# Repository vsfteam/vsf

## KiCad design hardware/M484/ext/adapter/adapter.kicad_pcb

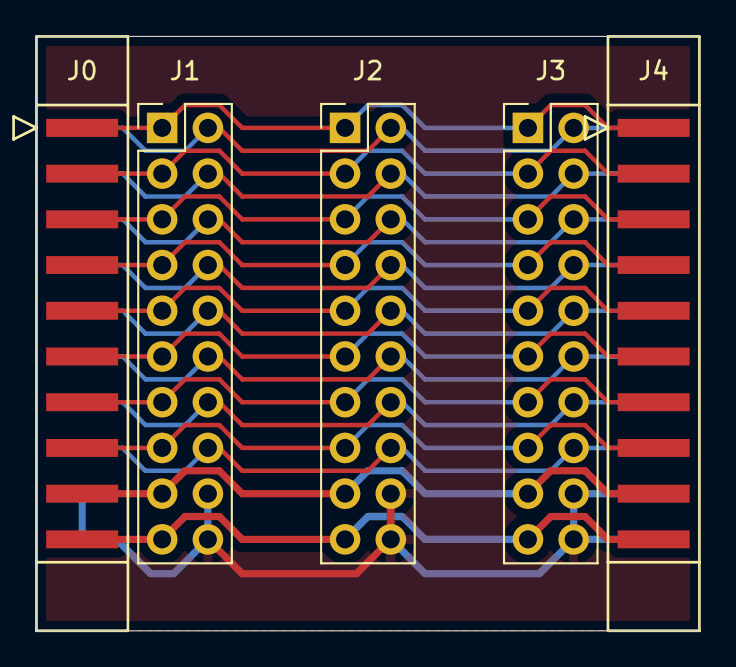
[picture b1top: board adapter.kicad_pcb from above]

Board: 2 copper layers, 36.8 x 33.0 mm, 5 parts (0 on the bottom side), 19 nets.

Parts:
J0, J4: Conn_02x10_Odd_Even; PinSocket_2x10_P2.54mm_Horizontal_2Layer
J1, J2, J3: Conn_02x10_Odd_Even; PinHeader_2x10_P2.54mm_Vertical

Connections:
/GND: J0.18, J0.20, J1.18, J1.20, J2.18, J2.20, J3.18, J3.20, J4.18, J4.20
/PB.0: J0.1, J1.1, J2.1, J3.1, J4.1
/PB.1: J0.2, J1.2, J2.2, J3.2, J4.2
/PB.2: J0.3, J1.3, J2.3, J3.3, J4.3
/PB.3: J0.4, J1.4, J2.4, J3.4, J4.4
/PB.4: J0.5, J1.5, J2.5, J3.5, J4.5
/PB.5: J0.6, J1.6, J2.6, J3.6, J4.6
/PB.6: J0.7, J1.7, J2.7, J3.7, J4.7
/PB.7: J0.8, J1.8, J2.8, J3.8, J4.8
/PB.8: J0.9, J1.9, J2.9, J3.9, J4.9
/PB.9: J0.10, J1.10, J2.10, J3.10, J4.10
/PB.10: J0.11, J1.11, J2.11, J3.11, J4.11
/PB.11: J0.12, J1.12, J2.12, J3.12, J4.12
/PB.12: J0.13, J1.13, J2.13, J3.13, J4.13
/PB.13: J0.14, J1.14, J2.14, J3.14, J4.14
/PB.14: J0.15, J1.15, J2.15, J3.15, J4.15
/PB.15: J0.16, J1.16, J2.16, J3.16, J4.16
/VCC: J0.17, J1.17, J2.17, J3.17, J4.17
/VCC5V: J0.19, J1.19, J2.19, J3.19, J4.19

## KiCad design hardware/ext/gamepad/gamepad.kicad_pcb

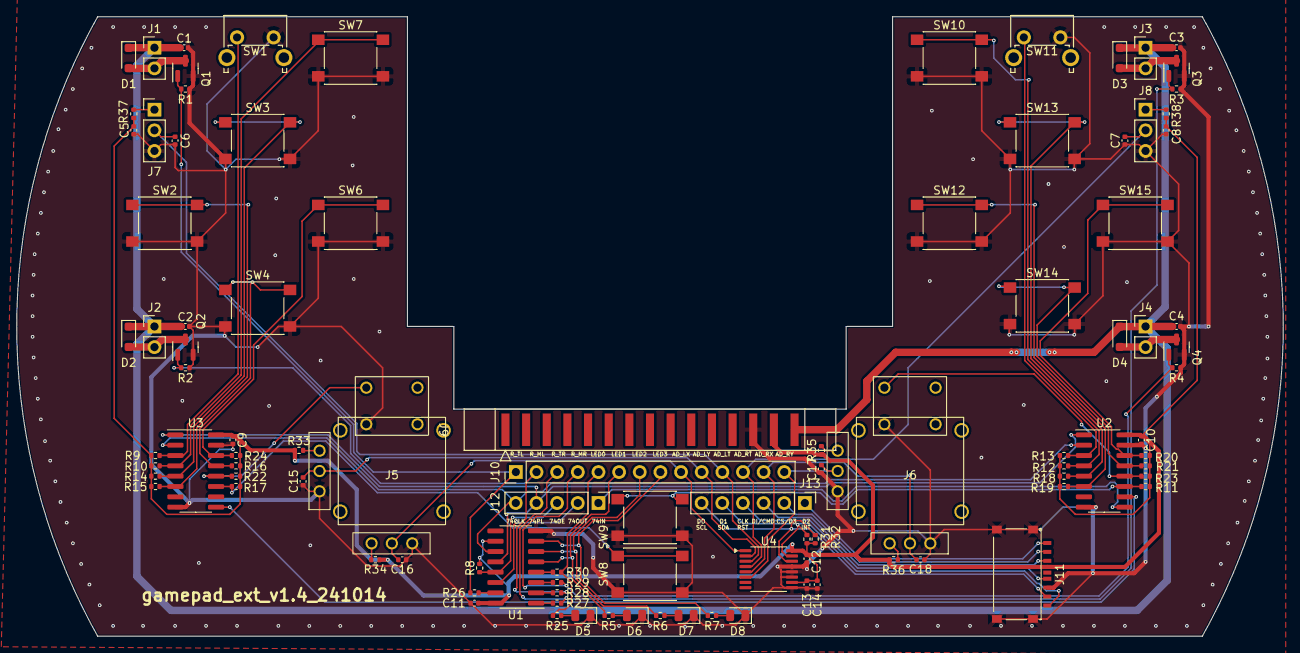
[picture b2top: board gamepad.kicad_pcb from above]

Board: 2 copper layers, 155.8 x 76.2 mm, 100 parts (0 on the bottom side), 64 nets.

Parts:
C1, C2, C3, C4, C13: 1uF; C_0402_1005Metric
C5, C7, C8, C15, C16, C17, C18: 0.1uF; C_0402_1005Metric
C6: 0.1nF; C_0402_1005Metric
C9, C10, C11, C12, C14: 100nF; C_0402_1005Metric
D1, D2, D3, D4: 1N4148; D_SOD-323_HandSoldering
D5, D6, D7, D8: LED; LED_0805_2012Metric
J1: Rumble_TL; PinHeader_1x02_P2.54mm_Vertical
J2: Rumble_ML; PinHeader_1x02_P2.54mm_Vertical
J3: Rumble_TR; PinHeader_1x02_P2.54mm_Vertical
J4: Rumble_MR; PinHeader_1x02_P2.54mm_Vertical
J5, J6: JoyStick
J7, J8: Conn_01x03; PinHeader_1x03_P2.54mm_Vertical
J9: Conn_02x15_Odd_Even; PinSocket_2x15_P2.54mm_Horizontal_2Layer
J10: Conn_01x14; PinHeader_1x14_P2.54mm_Vertical
J11: Micro_SD_Card_Det1; MicroSD_Tiny
J12: Conn_01x05; PinHeader_1x05_P2.54mm_Vertical
J13: Conn_01x06; PinHeader_1x06_P2.54mm_Vertical
Q1, Q2, Q3, Q4: AO3402; SOT-23
R1, R2, R3, R4: 47k; R_0402_1005Metric
R5, R6, R7, R25: 100; R_0402_1005Metric
R8, R9, R10, R11, R12, R13, R14, R15, R16, R17, R18, R19, R20, R21, R22, R23, R24, R31, R32: 4.7K; R_0402_1005Metric
R26, R27, R28, R29, R30: 0; R_0402_1005Metric
R33, R34, R35, R36, R37, R38: 2K; R_0402_1005Metric
SW1, SW11: SW_Push; SW_Tactile_SPST_Angled_PTS645Vx58-2LFS
SW2, SW3, SW4, SW6, SW7, SW8, SW9, SW10, SW12, SW13, SW14, SW15: SW_Push; SW_Push_1P1T_NO_6x6mm_H9.5mm
U1: 74HC595; SOP-16_3.9x9.9mm_P1.27mm
U2, U3: 74HC165; SOP-16_3.9x9.9mm_P1.27mm
U4: ADS7830; TSSOP-16_4.4x5mm_P0.65mm
VSF1: Gamepad_Outline

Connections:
/74CLK: J12.5, U1.11 (SRCLK), U2.2 (CP), U3.2 (CP)
/74IN: J12.1, U2.9 (Q7)
/74OE: J12.3, R8.1, U1.13 (~OE)
/74OUT: J12.2, U1.14 (SER)
/74PL: J12.4, U1.12 (RCLK), U2.1 (~PL), U3.1 (~PL)
/AD_LT: C6.2, J7.2, J10.11, U4.3 (CH2)
/AD_LX: C16.2, J5.2, J10.9, U4.1 (CH0)
/AD_LY: C15.2, J5.5, J10.10, U4.2 (CH1)
/AD_RT: C7.2, J8.2, J10.12, U4.4 (CH3)
/AD_RX: C18.2, J6.2, J10.13, U4.5 (CH4)
/AD_RY: C17.2, J6.5, J10.14, U4.6 (CH5)
/CLK: J11.5 (CLK), J13.4
/CS: J11.2 (DAT3/CD), J13.2
/DI: J11.3 (CMD), J13.3
/DO: J11.7 (DAT0), J13.6, R32.1, U4.14 (SCL)
/INT: J11.1 (DAT2), J13.1
/LED0: J10.5, R25.1, R30.2
/LED1: J10.6, R5.1, U1.5 (QF)
/LED2: J10.7, R6.1, U1.6 (QG)
/LED3: J10.8, R7.1, U1.7 (QH)
/RUMBLE_ML: J10.2, Q2.1 (G), R2.1, R28.2
/RUMBLE_MR: J10.4, Q4.1 (G), R4.1, R29.2
/RUMBLE_TL: J10.1, Q1.1 (G), R1.1, R26.2
/RUMBLE_TR: J10.3, Q3.1 (G), R3.1, R27.2
/SDA: J11.8 (DAT1), J13.5, R31.1, U4.15 (SDA)
/SW_HOME: R17.1, SW8.1, U3.11 (D0)
/SW_LB: R9.1, SW1.1, U3.3 (D4)
/SW_LD: R16.1, SW4.1, U3.13 (D2)
/SW_LL: R15.1, SW2.1, U3.6 (D7)
/SW_LR: R24.1, SW6.1, U3.14 (D3)
/SW_LS: J5.8, R22.1, U3.12 (D1)
/SW_LU: R14.1, SW3.1, U3.5 (D6)
/SW_ML: R10.1, SW7.1, U3.4 (D5)
/SW_MM: R11.1, SW9.1, U2.11 (D0)
/SW_MR: R12.1, SW10.1, U2.4 (D5)
/SW_RB: R13.1, SW11.1, U2.3 (D4)
/SW_RD: R21.1, SW14.1, U2.13 (D2)
/SW_RL: R19.1, SW12.1, U2.6 (D7)
/SW_RR: R20.1, SW15.1, U2.14 (D3)
/SW_RS: J6.8, R23.1, U2.12 (D1)
/SW_RU: R18.1, SW13.1, U2.5 (D6)
/VBAT: C1.1, C2.1, C3.1, C4.1, D1.1 (K), D2.1 (K), D3.1 (K), D4.1 (K), J1.1, J2.1, J3.1, J4.1, J9.29
/VCC: C5.2, C8.2, C9.1, C10.1, C11.1, C12.1, C13.2, C14.2, J9.27, J11.4 (VDD), R8.2, R9.2, R10.2, R11.2, R12.2, R13.2, R14.2, R15.2, R16.2, R17.2, R18.2, R19.2, R20.2, R21.2, R22.2, R23.2, R24.2, R31.2, R32.2, R33.1, R34.1, R35.1, R36.1, R37.2, R38.2, U1.10 (~SRCLR), U1.16 (VCC), U2.16 (VCC), U3.16 (VCC), U4.10 (REFin/REFout), U4.16 (VDD)
GND: C1.2, C2.2, C3.2, C4.2, C5.1, C6.1, C7.1, C8.1, C9.2, C10.2, C11.2, C12.2, C13.1, C14.1, C15.1, C16.1, C17.1, C18.1, D5.1 (K), D6.1 (K), D7.1 (K), D8.1 (K), J5.1, J5.4, J5.7, J6.1, J6.4, J6.7, J7.3, J8.3, J9.25, J11.6 (VSS), J11.10 (SHIELD), Q1.2 (S), Q2.2 (S), Q3.2 (S), Q4.2 (S), R1.2, R2.2, R3.2, R4.2, SW1.2, SW2.2, SW3.2, SW4.2, SW6.2, SW7.2, SW8.2, SW9.2, SW10.2, SW11.2, SW12.2, SW13.2, SW14.2, SW15.2, U1.8 (GND), U2.8 (GND), U2.15 (~CE), U3.8 (GND), U3.15 (~CE), U4.9 (GND), U4.11 (COM), U4.12 (A0), U4.13 (A1)
unnamed: D1.2 (A), J1.2, Q1.3 (D)
unnamed: D2.2 (A), J2.2, Q2.3 (D)
unnamed: D3.2 (A), J3.2, Q3.3 (D)
unnamed: D4.2 (A), J4.2, Q4.3 (D)
unnamed: D5.2 (A), R25.2
unnamed: D6.2 (A), R5.2
unnamed: D7.2 (A), R6.2
unnamed: D8.2 (A), R7.2
unnamed: J5.3, R34.2
unnamed: J5.6, R33.2
unnamed: J6.3, R36.2
unnamed: J6.6, R35.2
unnamed: J7.1, R37.1
unnamed: J8.1, R38.1
unnamed: R26.1, U1.15 (QA)
unnamed: R27.1, U1.1 (QB)
unnamed: R28.1, U1.2 (QC)
unnamed: R29.1, U1.3 (QD)
unnamed: R30.1, U1.4 (QE)
unnamed: U2.10 (DS), U3.9 (Q7)

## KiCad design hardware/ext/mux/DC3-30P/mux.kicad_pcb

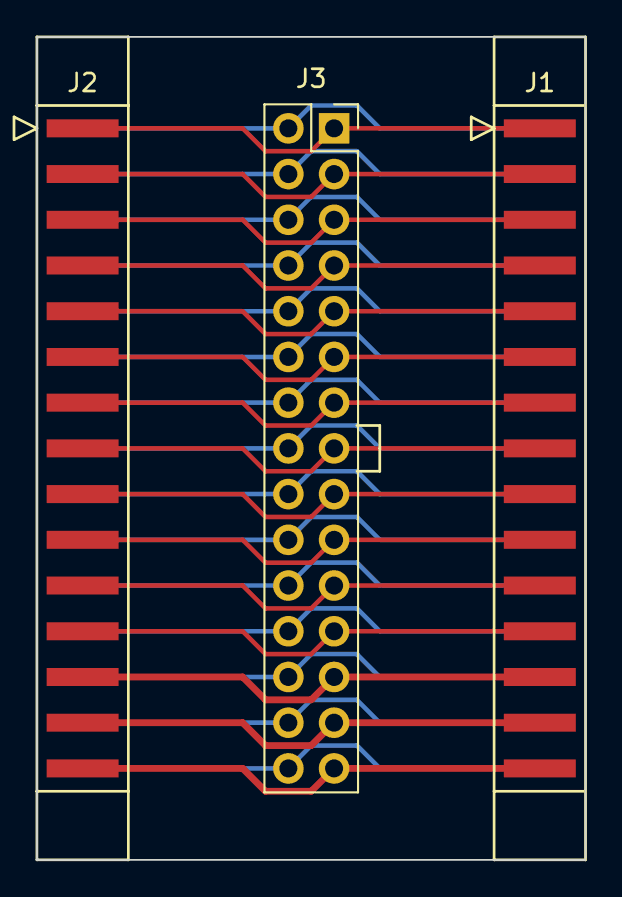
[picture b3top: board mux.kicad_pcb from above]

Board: 2 copper layers, 30.5 x 45.7 mm, 3 parts (0 on the bottom side), 30 nets.

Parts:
J1, J2: Conn_02x15_Odd_Even; PinSocket_2x15_P2.54mm_Horizontal_2Layer
J3: Conn_02x15_Odd_Even; PinSocket_2x15_P2.54mm_Vertical

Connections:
/5V: J1.29, J2.29, J3.29
/GND: J1.25, J2.25, J3.25
/GPIO0: J1.1, J2.1, J3.1
/GPIO1: J1.2, J2.2, J3.2
/GPIO2: J1.3, J2.3, J3.3
/GPIO3: J1.4, J2.4, J3.4
/GPIO4: J1.5, J2.5, J3.5
/GPIO5: J1.6, J2.6, J3.6
/GPIO6: J1.7, J2.7, J3.7
/GPIO7: J1.8, J2.8, J3.8
/GPIO8: J1.9, J2.9, J3.9
/GPIO9: J1.10, J2.10, J3.10
/GPIO10: J1.11, J2.11, J3.11
/GPIO11: J1.12, J2.12, J3.12
/GPIO12: J1.13, J2.13, J3.13
/GPIO13: J1.14, J2.14, J3.14
/GPIO14: J1.15, J2.15, J3.15
/GPIO15: J1.16, J2.16, J3.16
/GPIO16: J1.17, J2.17, J3.17
/GPIO17: J1.18, J2.18, J3.18
/GPIO18: J1.19, J2.19, J3.19
/GPIO19: J1.20, J2.20, J3.20
/GPIO20: J1.21, J2.21, J3.21
/GPIO21: J1.22, J2.22, J3.22
/GPIO22: J1.23, J2.23, J3.23
/GPIO23: J1.24, J2.24, J3.24
/PWREN: J1.30, J2.30, J3.30
/USB_DM: J1.26, J2.26, J3.26
/USB_DP: J1.28, J2.28, J3.28
/VCC: J1.27, J2.27, J3.27

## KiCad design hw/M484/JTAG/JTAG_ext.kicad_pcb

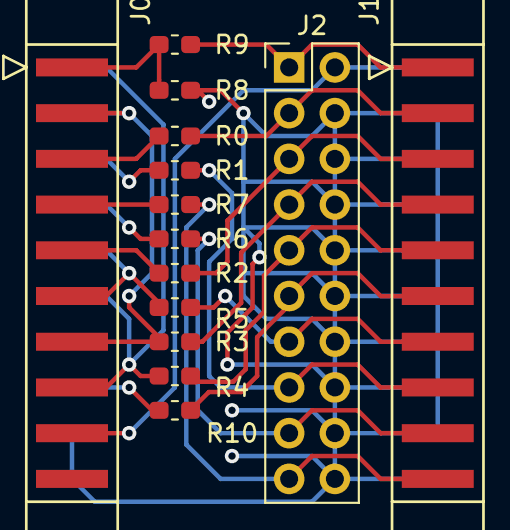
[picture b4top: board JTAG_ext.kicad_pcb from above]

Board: 2 copper layers, 14 parts (0 on the bottom side), 22 nets.

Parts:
J0, J1: Conn_02x10_Odd_Even; PinSocket_2x10_P2.54mm_Horizontal_2Layer
J2: Conn_02x10_Odd_Even; PinHeader_2x10_P2.54mm_Vertical
R0, R1, R2, R3, R4, R5, R6, R7, R10: 22; R_0603_1608Metric_Pad1.05x0.95mm_HandSolder
R8, R9: 10K; R_0603_1608Metric_Pad1.05x0.95mm_HandSolder

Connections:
/EADC0_CH0: J0.1, R8.2, R9.2
/GND: J0.18, J0.20, J1.4, J1.6, J1.8, J1.10, J1.12, J1.14, J1.16, J1.18, J1.20, J2.4, J2.6, J2.8, J2.10, J2.12, J2.14, J2.16, J2.18, J2.20, R8.1
/PB.1: J0.2, J0.12, J0.15, R4.2
/PB.4: J0.5, R0.2
/PB.5: J0.6, R1.2
/PB.6: J0.7, R7.2
/PB.7: J0.8, R6.2
/PB.8: J0.9, R2.2
/PB.10: J0.10, J0.11, R5.2
/PB.12: J0.3, J0.4, J0.13, R3.2
/PB.15: J0.16, R10.2
/RTCK: J1.11, J2.11, R10.1
/RXD: J1.19, J2.19, R7.1
/TCK: J1.9, J2.9, R4.1
/TDI: J1.5, J2.5, R2.1
/TDO: J1.13, J2.13, R5.1
/TMS: J1.7, J2.7, R3.1
/TXD: J1.17, J2.17, R6.1
/VCC: J0.17, J1.2, J2.2
/Vref: J1.1, J2.1, R9.1
/nRST: J1.15, J2.15, R1.1
/nTRST: J1.3, J2.3, R0.1
